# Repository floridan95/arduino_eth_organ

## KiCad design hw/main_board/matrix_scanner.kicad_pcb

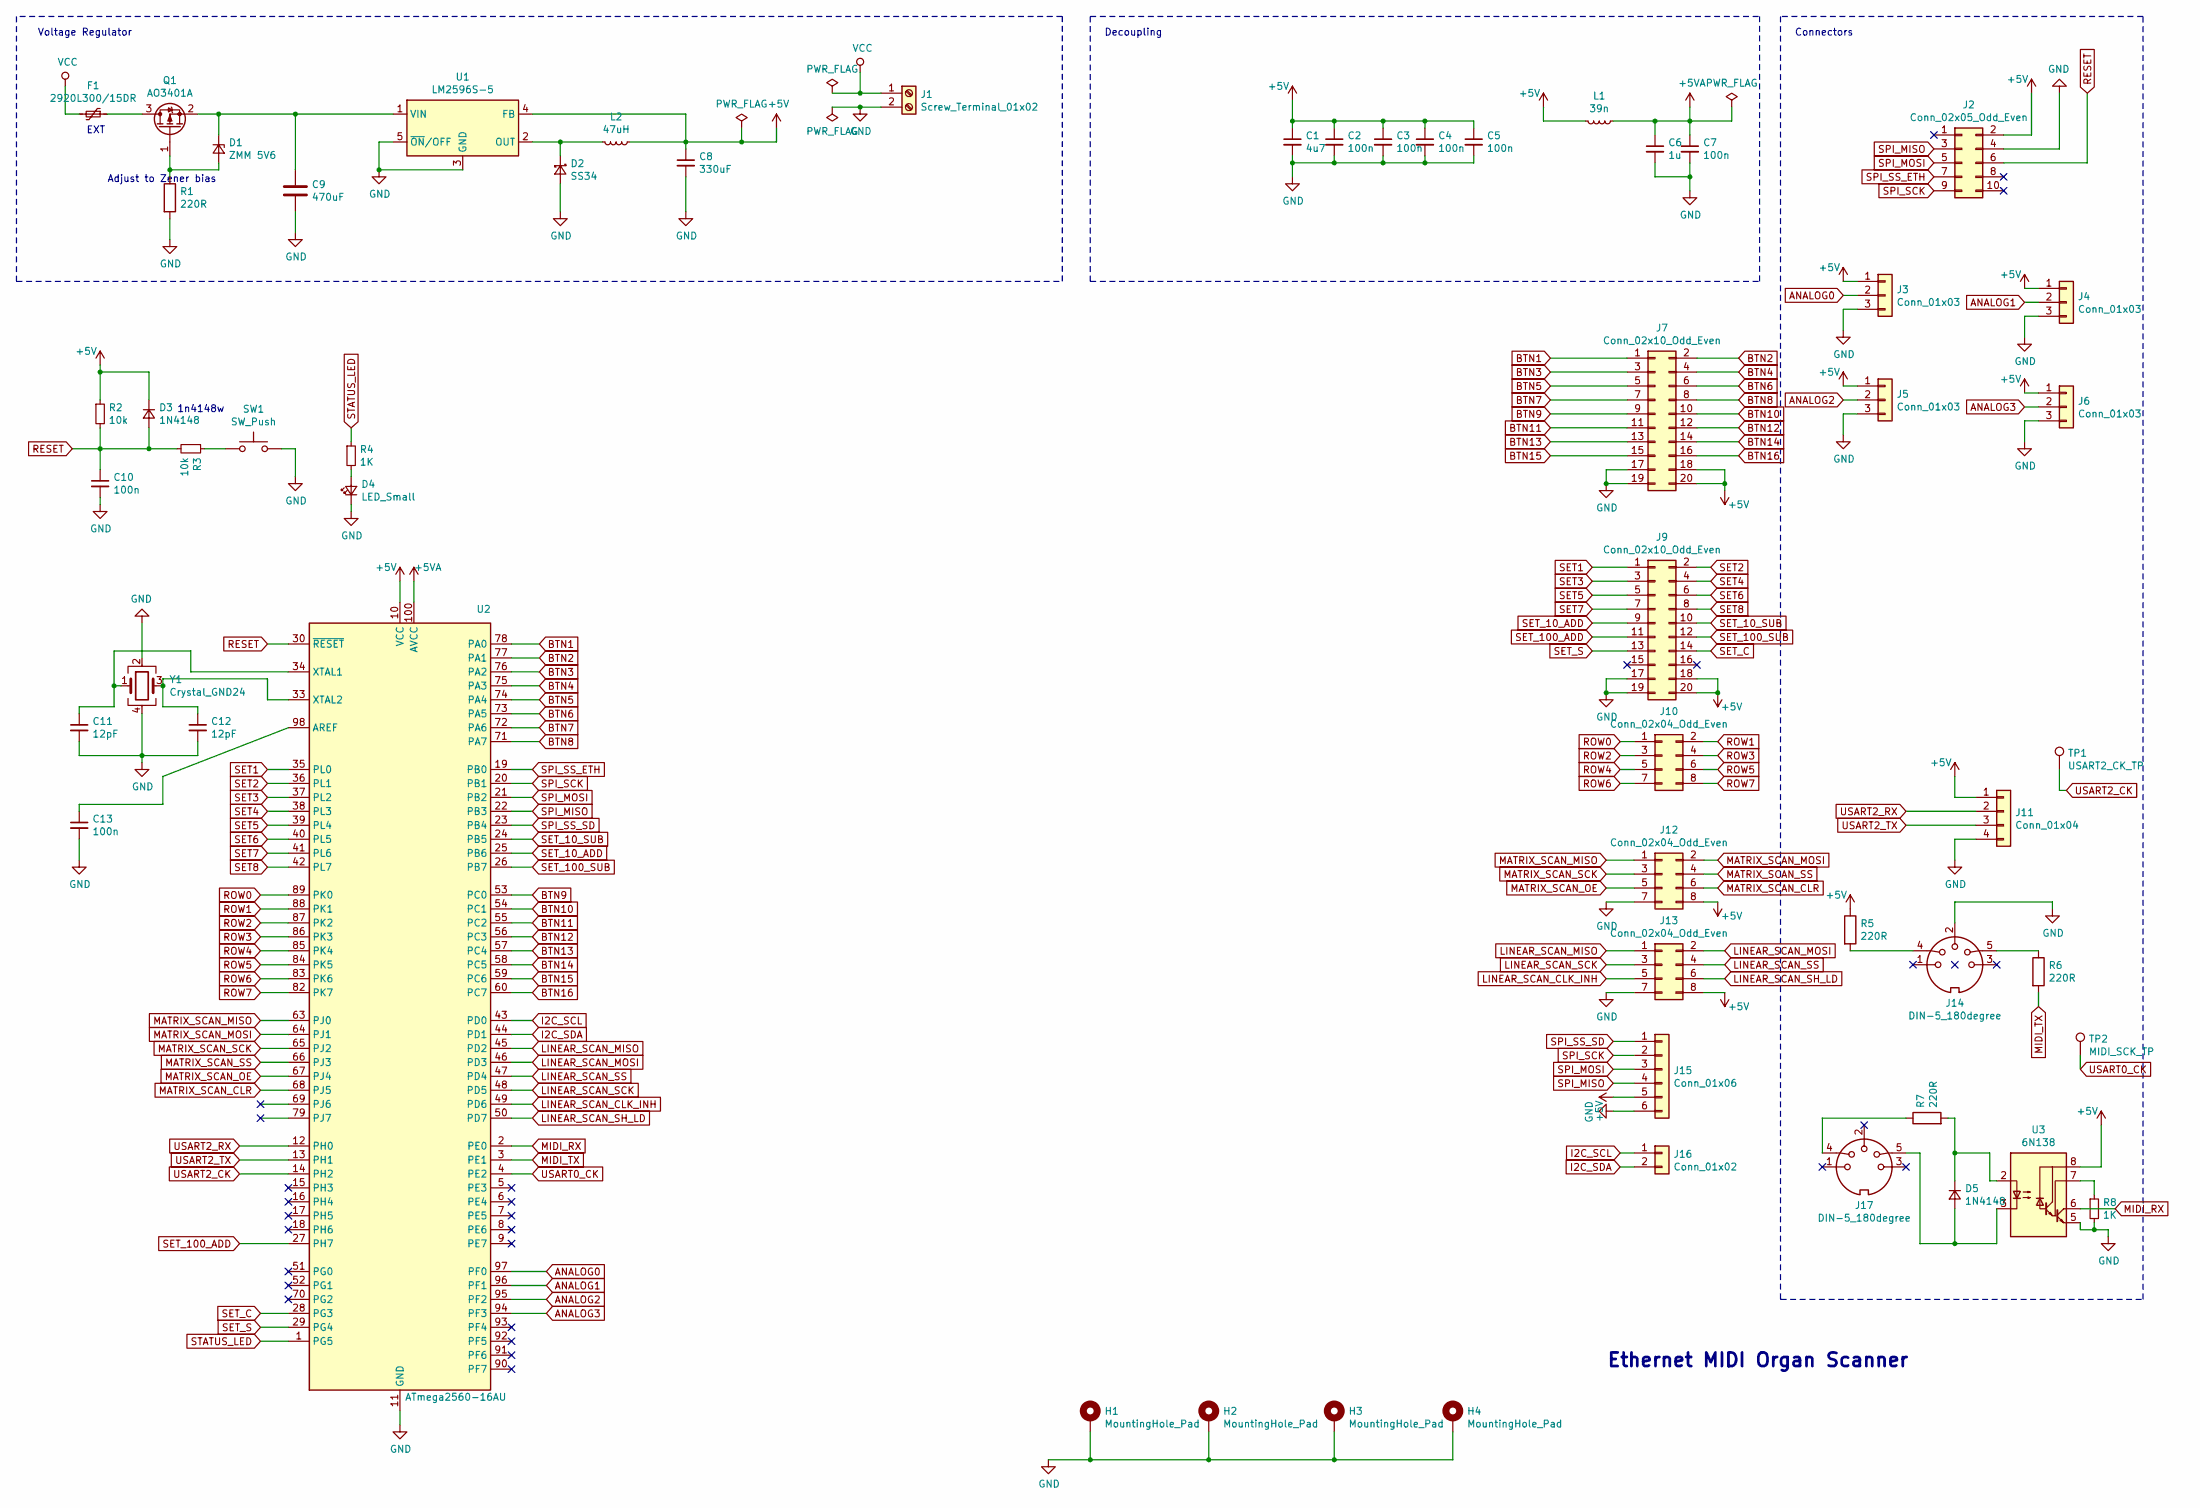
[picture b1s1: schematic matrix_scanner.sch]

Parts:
C1: 4u7; C_0603_1608Metric_Pad1.05x0.95mm_HandSolder; LCSC C1623
C2, C3, C4, C5, C7, C10, C13: 100n; C_0603_1608Metric_Pad1.05x0.95mm_HandSolder; LCSC C14663
C6: 1u; C_0603_1608Metric_Pad1.05x0.95mm_HandSolder; LCSC C15849
C8: 330uF; CP_Radial_D10.0mm_P5.00mm
C9: 470uF; CP_Radial_D10.0mm_P5.00mm
C11, C12: 12pF; C_0402_1005Metric; LCSC C1547
D1: ZMM 5V6; D_MiniMELF; LCSC C8062
D2: SS34; D_SMA; LCSC C8678
D3, D5: 1N4148; D_SOD-123; LCSC C81598
D4: LED_Small; LED_0603_1608Metric; LCSC C72038
F1: 2920L300/15DR; Fuse_2920_7451Metric; LCSC C207089
H1, H2, H3, H4: MountingHole_Pad; MountingHole_4.3mm_M4_Pad_Via
J1: Screw_Terminal_01x02; TerminalBlock_4Ucon_1x02_P3.50mm_Horizontal
J2: Conn_02x05_Odd_Even; PinSocket_2x05_P2.54mm_Vertical
J3, J4, J5, J6: Conn_01x03; PinSocket_1x03_P2.54mm_Vertical
J7, J9: Conn_02x10_Odd_Even; IDC-Header_2x10_P2.54mm_Vertical_Lock
J10, J12, J13: Conn_02x04_Odd_Even; PinHeader_2x04_P2.54mm_Vertical
J11: Conn_01x04; PinHeader_1x04_P2.54mm_Vertical
J14, J17: DIN-5_180degree; MIDI_DIN5
J15: Conn_01x06; PinHeader_1x06_P2.54mm_Vertical
J16: Conn_01x02; PinHeader_1x02_P2.54mm_Vertical
L1: 39n; L_0402_1005Metric; LCSC C26443
L2: 47uH; L_Bourns_SRR1260; LCSC C115409
Q1: AO3401A; SOT-23; LCSC C15127
R1: 220R; R_1206_3216Metric_Pad1.42x1.75mm_HandSolder; LCSC C17957
R2, R3: 10k; R_0805_2012Metric; LCSC C17414
R4, R8: 1K; R_0805_2012Metric; LCSC C17513
R5, R6, R7: 220R; R_1206_3216Metric; LCSC C17957
SW1: SW_Push; PinHeader_1x02_P2.54mm_Vertical
TP1: USART2_CK_TP; PinHeader_1x01_P2.54mm_Vertical
TP2: MIDI_SCK_TP; PinHeader_1x01_P2.54mm_Vertical
U1: LM2596S-5; TO-263-5_TabPin3; LCSC C10002
U2: ATmega2560-16AU; TQFP-100_14x14mm_P0.5mm; LCSC C22460
U3: 6N138; SMDIP-8_W9.53mm; LCSC C188666
Y1: Crystal_GND24; Crystal_SMD_3225-4Pin_3.2x2.5mm; LCSC C13738

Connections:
+5V: C1.1, C2.1, C3.1, C4.1, C5.1, C8.1, D3.1 (K), J2.2, J3.1, J4.1, J5.1, J6.1, J7.18, J7.20, J9.18, J9.20, J11.1, J12.8, J13.8, J15.5, L1.2, L2.1, R2.1, R5.1, U1.4 (FB), U2.10 (VCC), U2.31 (VCC), U2.61 (VCC), U2.80 (VCC), U3.8 (VCC)
+5VA: C6.1, C7.1, L1.1, U2.100 (AVCC)
ANALOG0: J3.2, U2.97 (PF0)
ANALOG1: J4.2, U2.96 (PF1)
ANALOG2: J5.2, U2.95 (PF2)
ANALOG3: J6.2, U2.94 (PF3)
BTN1: J7.1, U2.78 (PA0)
BTN2: J7.2, U2.77 (PA1)
BTN3: J7.3, U2.76 (PA2)
BTN4: J7.4, U2.75 (PA3)
BTN5: J7.5, U2.74 (PA4)
BTN6: J7.6, U2.73 (PA5)
BTN7: J7.7, U2.72 (PA6)
BTN8: J7.8, U2.71 (PA7)
BTN9: J7.9, U2.53 (PC0)
BTN10: J7.10, U2.54 (PC1)
BTN11: J7.11, U2.55 (PC2)
BTN12: J7.12, U2.56 (PC3)
BTN13: J7.13, U2.57 (PC4)
BTN14: J7.14, U2.58 (PC5)
BTN15: J7.15, U2.59 (PC6)
BTN16: J7.16, U2.60 (PC7)
GND: C1.2, C2.2, C3.2, C4.2, C5.2, C6.2, C7.2, C8.2, C9.2, C10.2, C11.2, C12.2, C13.2, D2.2 (A), D4.1 (K), H1.1, H2.1, H3.1, H4.1, J1.2, J2.4, J3.3, J4.3, J5.3, J6.3, J7.17, J7.19, J9.17, J9.19, J11.4, J12.7, J13.7, J14.2, J15.6, R1.2, R8.2, SW1.2, U1.3 (GND), U1.5 (~ON~/OFF), U2.11 (GND), U2.32 (GND), U2.62 (GND), U2.81 (GND), U2.99 (GND), U3.5 (GND), Y1.2, Y1.4
I2C_SCL: J16.1, U2.43 (PD0)
I2C_SDA: J16.2, U2.44 (PD1)
LINEAR_SCAN_CLK_INH: J13.5, U2.49 (PD6)
LINEAR_SCAN_MISO: J13.1, U2.45 (PD2)
LINEAR_SCAN_MOSI: J13.2, U2.46 (PD3)
LINEAR_SCAN_SCK: J13.3, U2.48 (PD5)
LINEAR_SCAN_SH_LD: J13.6, U2.50 (PD7)
LINEAR_SCAN_SS: J13.4, U2.47 (PD4)
MATRIX_SCAN_CLR: J12.6, U2.68 (PJ5)
MATRIX_SCAN_MISO: J12.1, U2.63 (PJ0)
MATRIX_SCAN_MOSI: J12.2, U2.64 (PJ1)
MATRIX_SCAN_OE: J12.5, U2.67 (PJ4)
MATRIX_SCAN_SCK: J12.3, U2.65 (PJ2)
MATRIX_SCAN_SS: J12.4, U2.66 (PJ3)
MIDI_RX: U2.2 (PE0), U3.6 (VO2)
MIDI_TX: R6.2, U2.3 (PE1)
unnamed: C9.1, D1.1 (K), Q1.2 (S), U1.1 (VIN)
unnamed: C11.1, U2.34 (XTAL1), Y1.1
unnamed: C12.1, U2.33 (XTAL2), Y1.3
unnamed: C13.1, U2.98 (AREF)
unnamed: D1.2 (A), Q1.1 (G), R1.1
unnamed: D2.1 (K), L2.2, U1.2 (OUT)
unnamed: D4.2 (A), R4.2
unnamed: D5.1 (K), R7.2, U3.2 (C1)
unnamed: D5.2 (A), J17.5, U3.3 (C2)
unnamed: F1.1, Q1.3 (D)
unnamed: J14.4, R5.2
unnamed: J14.5, R6.1
unnamed: J17.4, R7.1
unnamed: R3.1, SW1.1
unnamed: R8.1, U3.7 (VO1)
RESET: C10.1, D3.2 (A), J2.6, R2.2, R3.2, U2.30 (~RESET)
ROW0: J10.1, U2.89 (PK0)
ROW1: J10.2, U2.88 (PK1)
ROW2: J10.3, U2.87 (PK2)
ROW3: J10.4, U2.86 (PK3)
ROW4: J10.5, U2.85 (PK4)
ROW5: J10.6, U2.84 (PK5)
ROW6: J10.7, U2.83 (PK6)
ROW7: J10.8, U2.82 (PK7)
SET1: J9.1, U2.35 (PL0)
SET2: J9.2, U2.36 (PL1)
SET3: J9.3, U2.37 (PL2)
SET4: J9.4, U2.38 (PL3)
SET5: J9.5, U2.39 (PL4)
SET6: J9.6, U2.40 (PL5)
SET7: J9.7, U2.41 (PL6)
SET8: J9.8, U2.42 (PL7)
SET_10_ADD: J9.9, U2.25 (PB6)
SET_10_SUB: J9.10, U2.24 (PB5)
SET_100_ADD: J9.11, U2.27 (PH7)
SET_100_SUB: J9.12, U2.26 (PB7)
SET_C: J9.14, U2.28 (PG3)
SET_S: J9.13, U2.29 (PG4)
SPI_MISO: J2.3, J15.4, U2.22 (PB3)
SPI_MOSI: J2.5, J15.3, U2.21 (PB2)
SPI_SCK: J2.9, J15.2, U2.20 (PB1)
SPI_SS_ETH: J2.7, U2.19 (PB0)
SPI_SS_SD: J15.1, U2.23 (PB4)
STATUS_LED: R4.1, U2.1 (PG5)
USART0_CK: TP2.1, U2.4 (PE2)
USART2_CK: TP1.1, U2.14 (PH2)
USART2_RX: J11.2, U2.12 (PH0)
USART2_TX: J11.3, U2.13 (PH1)
VCC: F1.2, J1.1

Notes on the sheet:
1n4148w
Adjust to Zener bias
Voltage Regulator
Decoupling
Connectors
Ethernet MIDI Organ Scanner
EXT

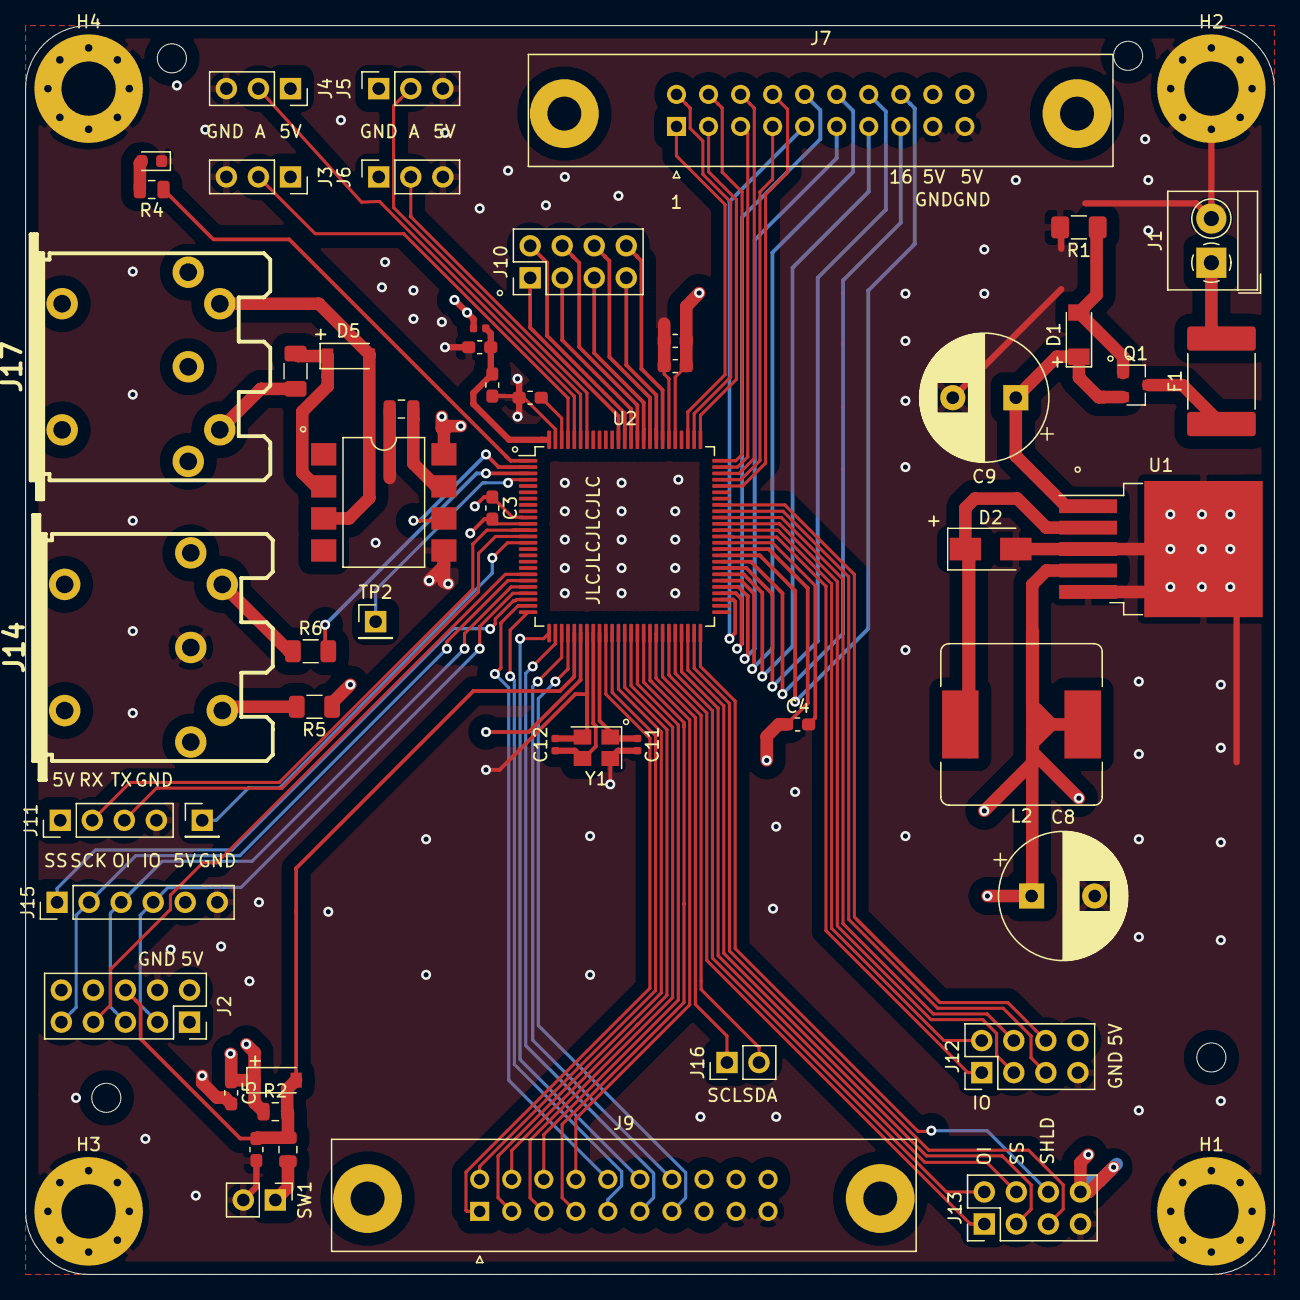
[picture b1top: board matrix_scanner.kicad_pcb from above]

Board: 4 copper layers, 99.0 x 99.0 mm, 57 parts (0 on the bottom side), 88 nets.

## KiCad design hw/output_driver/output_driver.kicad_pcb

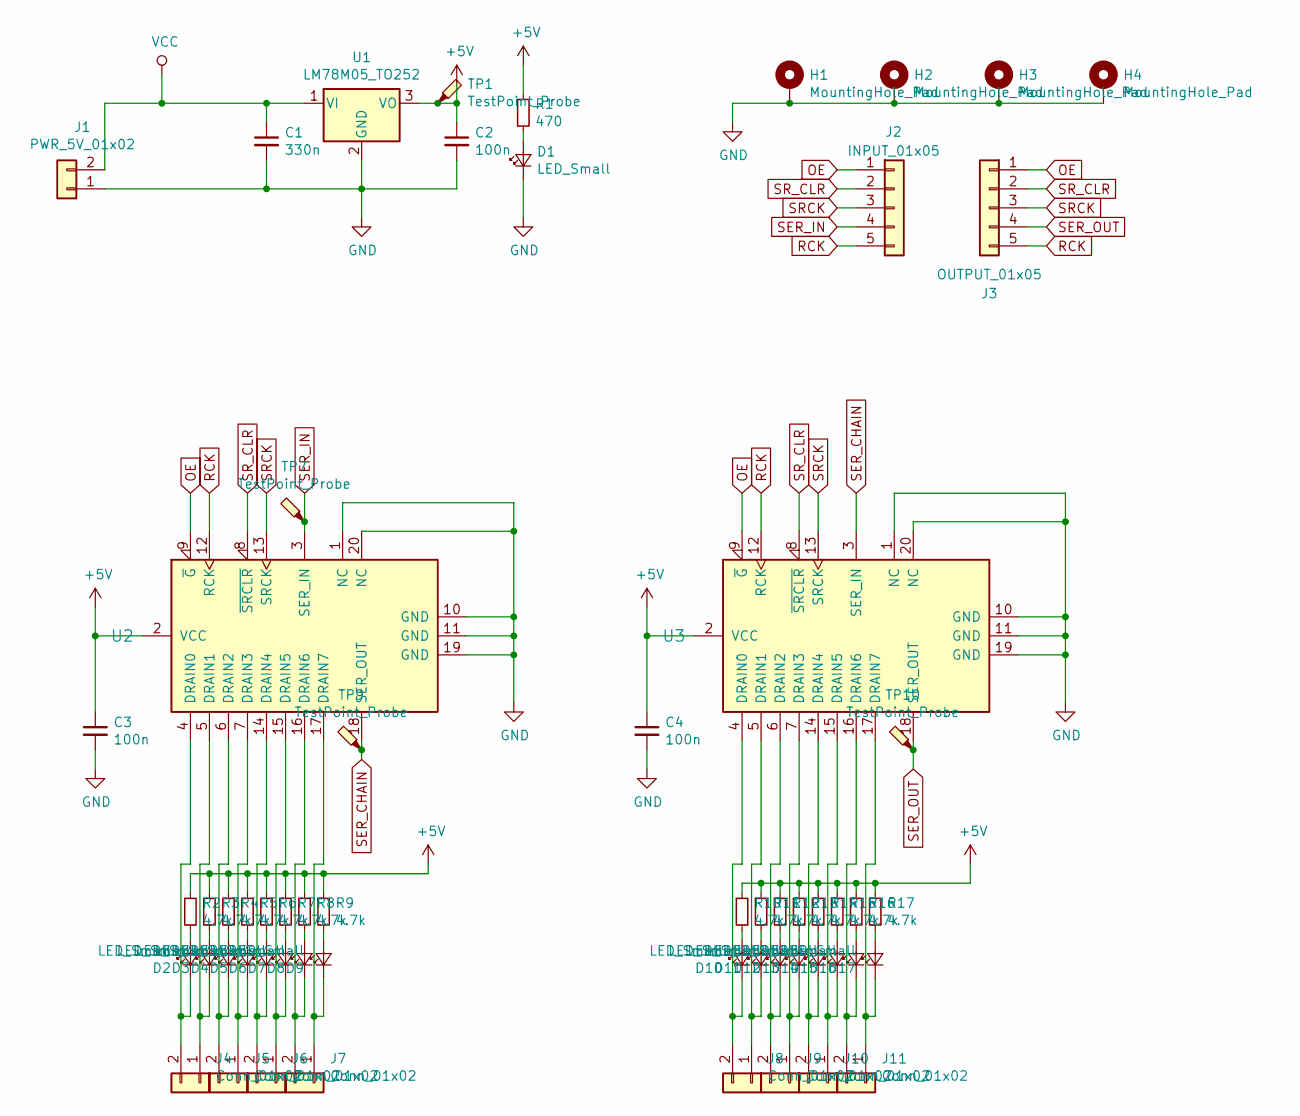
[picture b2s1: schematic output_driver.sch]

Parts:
C1: 330n; C_0805_2012Metric_Pad1.15x1.40mm_HandSolder; LCSC C1740
C2, C3, C4: 100n; C_0805_2012Metric_Pad1.15x1.40mm_HandSolder; JLCPCB C24497
D1, D2, D3, D4, D5, D6, D7, D8, D9, D10, D11, D12, D13, D14, D15, D16, D17: LED_Small; LED_0805_2012Metric_Pad1.15x1.40mm_HandSolder; JLCPCB C2296
H1, H2, H3, H4: MountingHole_Pad; MountingHole_4.3mm_M4_Pad_Via
J1: PWR_5V_01x02; TerminalBlock_4Ucon_1x02_P3.50mm_Horizontal
J2: INPUT_01x05; PinHeader_1x05_P2.54mm_Vertical
J3: OUTPUT_01x05; PinHeader_1x05_P2.54mm_Vertical
J4, J5, J6, J7, J8, J9, J10, J11: Conn_01x02; PinHeader_1x02_P2.54mm_Vertical
R1: 470; R_0805_2012Metric_Pad1.15x1.40mm_HandSolder; JLCPCB C17710
R2, R3, R4, R5, R6, R7, R8, R9, R10, R11, R12, R13, R14, R15, R16, R17: 4.7k; R_0805_2012Metric_Pad1.15x1.40mm_HandSolder; JLCPCB C17673
TP1, TP7, TP9, TP10: TestPoint_Probe; TestPoint_Pad_D2.5mm
U1: LM78M05_TO252; TO-252-2; JLCPCB C58069
U2, U3: TPIC6B595N; SOIC-20W_7.5x12.8mm_P1.27mm; JLCPCB C7094

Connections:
+5V: C2.1, C3.1, C4.1, R1.1, R2.1, R3.1, R4.1, R5.1, R6.1, R7.1, R8.1, R9.1, R10.1, R11.1, R12.1, R13.1, R14.1, R15.1, R16.1, R17.1, TP1.1, U1.3 (VO), U2.2 (VCC), U3.2 (VCC)
GND: C1.2, C2.2, C3.2, C4.2, D1.1 (K), H1.1, H2.1, H3.1, H4.1, J1.1, U1.2 (GND), U2.1 (NC), U2.10 (GND), U2.11 (GND), U2.19 (GND), U2.20 (NC), U3.1 (NC), U3.10 (GND), U3.11 (GND), U3.19 (GND), U3.20 (NC)
unnamed: D1.2 (A), R1.2
unnamed: D2.1 (K), J4.2, U2.4 (DRAIN0)
unnamed: D2.2 (A), R2.2
unnamed: D3.1 (K), J4.1, U2.5 (DRAIN1)
unnamed: D3.2 (A), R3.2
unnamed: D4.1 (K), J5.2, U2.6 (DRAIN2)
unnamed: D4.2 (A), R4.2
unnamed: D5.1 (K), J5.1, U2.7 (DRAIN3)
unnamed: D5.2 (A), R5.2
unnamed: D6.1 (K), J6.2, U2.14 (DRAIN4)
unnamed: D6.2 (A), R6.2
unnamed: D7.1 (K), J6.1, U2.15 (DRAIN5)
unnamed: D7.2 (A), R7.2
unnamed: D8.1 (K), J7.2, U2.16 (DRAIN6)
unnamed: D8.2 (A), R8.2
unnamed: D9.1 (K), J7.1, U2.17 (DRAIN7)
unnamed: D9.2 (A), R9.2
unnamed: D10.1 (K), J8.2, U3.4 (DRAIN0)
unnamed: D10.2 (A), R10.2
unnamed: D11.1 (K), J8.1, U3.5 (DRAIN1)
unnamed: D11.2 (A), R11.2
unnamed: D12.1 (K), J9.2, U3.6 (DRAIN2)
unnamed: D12.2 (A), R12.2
unnamed: D13.1 (K), J9.1, U3.7 (DRAIN3)
unnamed: D13.2 (A), R13.2
unnamed: D14.1 (K), J10.2, U3.14 (DRAIN4)
unnamed: D14.2 (A), R14.2
unnamed: D15.1 (K), J10.1, U3.15 (DRAIN5)
unnamed: D15.2 (A), R15.2
unnamed: D16.1 (K), J11.2, U3.16 (DRAIN6)
unnamed: D16.2 (A), R16.2
unnamed: D17.1 (K), J11.1, U3.17 (DRAIN7)
unnamed: D17.2 (A), R17.2
OE: J2.1, J3.1, U2.9 (~G), U3.9 (~G)
RCK: J2.5, J3.5, U2.12 (RCK), U3.12 (RCK)
SER_CHAIN: TP9.1, U2.18 (SER_OUT), U3.3 (SER_IN)
SER_IN: J2.4, TP7.1, U2.3 (SER_IN)
SER_OUT: J3.4, TP10.1, U3.18 (SER_OUT)
SRCK: J2.3, J3.3, U2.13 (SRCK), U3.13 (SRCK)
SR_CLR: J2.2, J3.2, U2.8 (~SRCLR), U3.8 (~SRCLR)
VCC: C1.1, J1.2, U1.1 (VI)

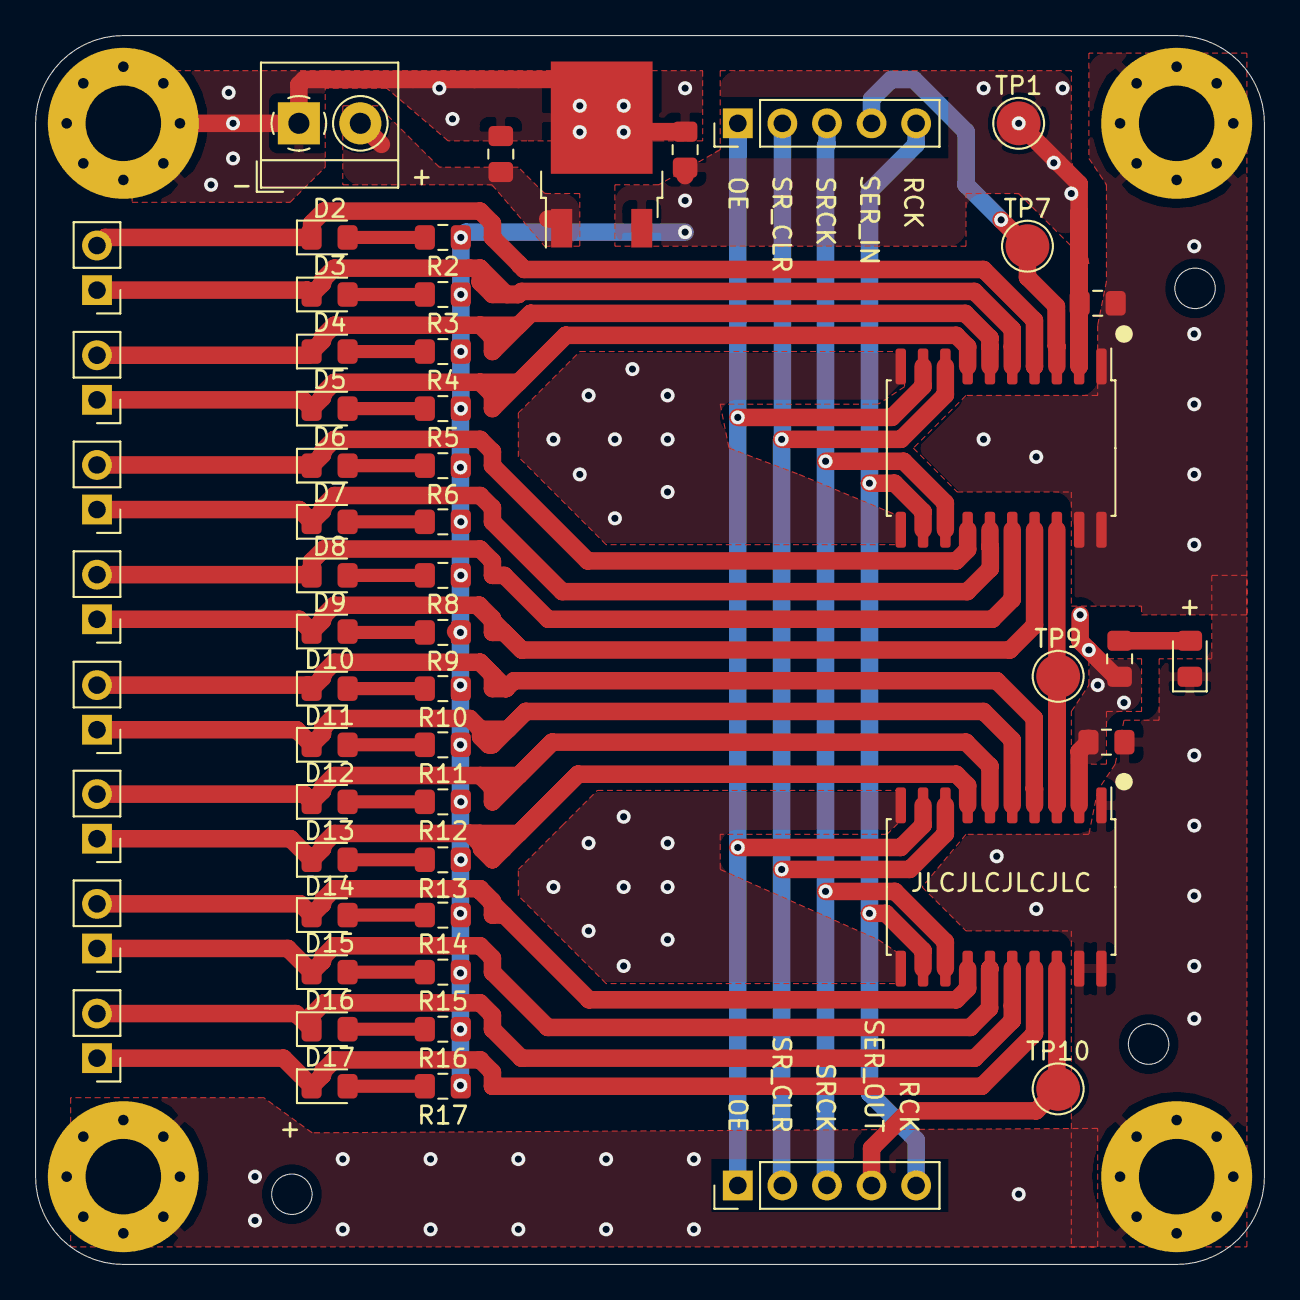
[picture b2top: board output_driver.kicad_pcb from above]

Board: 2 copper layers, 70.0 x 70.0 mm, 60 parts (0 on the bottom side), 43 nets.

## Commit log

2020-12-08 Initial PIO project changing git author configs
2020-12-08 Now its the right project
2020-12-08 Add hardware files
2020-12-14 MIDI csatorna kiosztas
2020-12-14 MatrixKeyboardScanning
2020-12-14 Send out events from MIDI matrix
2020-12-14 Couplers initial impl
2020-12-14 typo at addCoupler signature
2020-12-15 InputShiftReg and prettify
2020-12-15 ethernet_bandwidth_test
